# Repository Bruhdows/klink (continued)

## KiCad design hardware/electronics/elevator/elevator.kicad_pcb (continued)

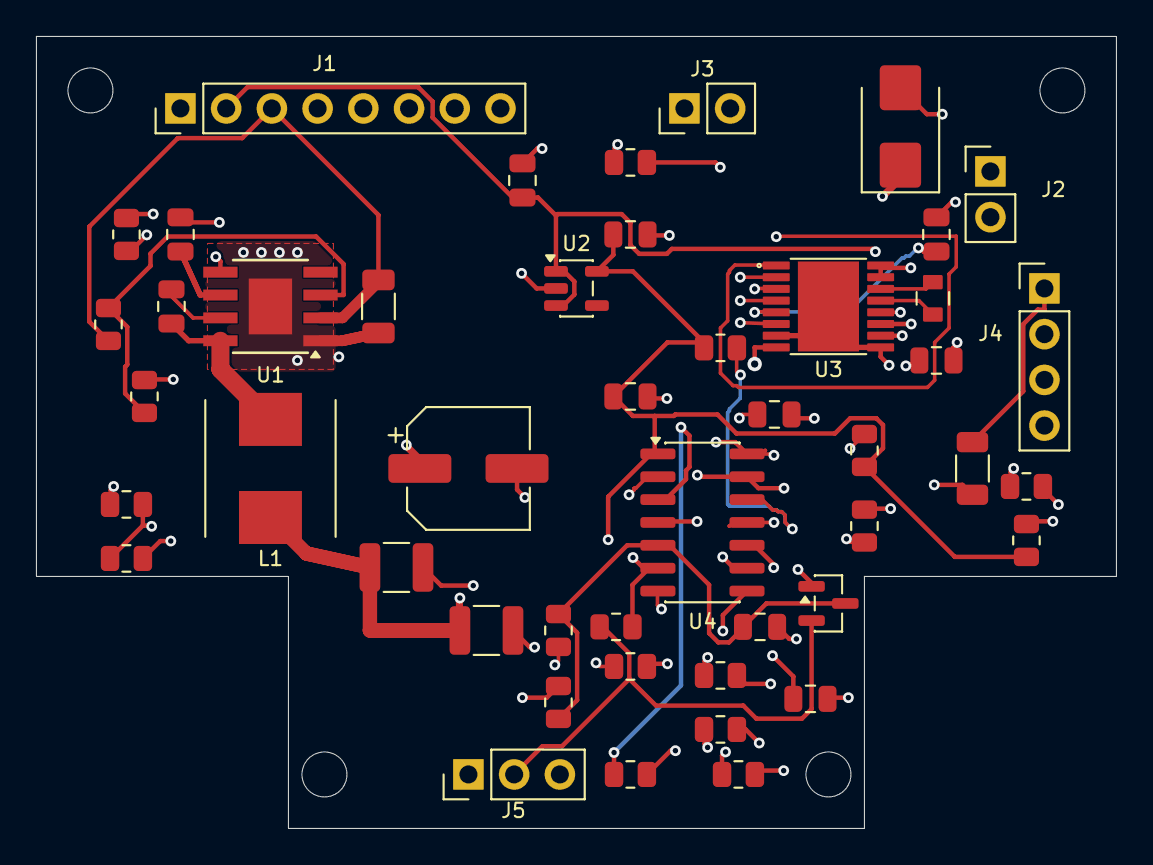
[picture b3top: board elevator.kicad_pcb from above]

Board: 4 copper layers, 60.0 x 44.0 mm, 51 parts (0 on the bottom side), 31 nets.

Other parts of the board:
H1, H2, H3, H4: MountingHole_2.5mm

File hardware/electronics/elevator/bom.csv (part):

Reference,Value,MPN,Alternate,TCR,Footprint,Quantity,purchase_url,unit_price,currency,price_status,checked_date,lcsc_reference
C1,10uF 50V X7R,C3216X7R1H106K160AC,,,Capacitor_SMD:C_1206_3216Metric,1,https://www.mouser.com/ProductDetail/TDK/C3216X7R1H106K160AC,0.35,USD,engineering allowance; NOT a verified supplier price,,
C2,100nF 50V X7R,C2012X7R1H104K125AE,,,Capacitor_SMD:C_0805_2012Metric,1,https://www.mouser.com/ProductDetail/TDK/C2012X7R1H104K125AE,0.1,USD,engineering allowance; NOT a verified supplier price,,
C3,1uF 16V,C2012X7R1H105K125AB,,,Capacitor_SMD:C_0805_2012Metric,1,https://www.mouser.com/ProductDetail/TDK/C2012X7R1H105K125AB,0.1,USD,engineering allowance; NOT a verified supplier price,,
C4,22uF 25V X7R,C1210C226K3RACTU,,,Capacitor_SMD:C_1210_3225Metric,1,https://www.mouser.com/ProductDetail/KEMET/C1210C226K3RACTU,0.35,USD,engineering allowance; NOT a verified supplier price,,
C5,22uF 25V X7R,C1210C226K3RACTU,,,Capacitor_SMD:C_1210_3225Metric,1,https://www.mouser.com/ProductDetail/KEMET/C1210C226K3RACTU,0.35,USD,engineering allowance; NOT a verified supplier price,,
C6,100uF 25V,EEH-ZC1E101XP,,,Capacitor_SMD:CP_Elec_6.3x7.7,1,https://www.mouser.com/ProductDetail/Panasonic/EEH-ZC1E101XP,1.5,USD,engineering allowance; NOT a verified supplier price,,
C7,1uF 16V,C2012X7R1H105K125AB,,,Capacitor_SMD:C_0805_2012Metric,1,https://www.mouser.com/ProductDetail/TDK/C2012X7R1H105K125AB,0.1,USD,engineering allowance; NOT a verified supplier price,,
C8,4.7uF 16V,C2012X7R1C475K125AB,,,Capacitor_SMD:C_0805_2012Metric,1,https://www.mouser.com/ProductDetail/TDK/C2012X7R1C475K125AB,0.1,USD,engineering allowance; NOT a verified supplier price,,
C9,100nF 50V X7R,C2012X7R1H104K125AE,,,Capacitor_SMD:C_0805_2012Metric,1,https://www.mouser.com/ProductDetail/TDK/C2012X7R1H104K125AE,0.1,USD,engineering allowance; NOT a verified supplier price,,
C10,100nF 50V X7R,C2012X7R1H104K125AE,,,Capacitor_SMD:C_0805_2012Metric,1,https://www.mouser.com/ProductDetail/TDK/C2012X7R1H104K125AE,0.1,USD,engineering allowance; NOT a verified supplier price,,
C11,22nF 50V,C2012C0G1H223J125AA,,,Klink:C_TDK_C2012_Reflow,1,https://www.mouser.com/ProductDetail/TDK/C2012C0G1H223J125AA,0.1,USD,engineering allowance; NOT a verified supplier price,,
C12,100nF 50V X7R,C2012X7R1H104K125AE,,,Capacitor_SMD:C_0805_2012Metric,1,https://www.mouser.com/ProductDetail/TDK/C2012X7R1H104K125AE,0.1,USD,engineering allowance; NOT a verified supplier price,,
C13,100nF 50V X7R,C2012X7R1H104K125AE,,,Capacitor_SMD:C_0805_2012Metric,1,https://www.mouser.com/ProductDetail/TDK/C2012X7R1H104K125AE,0.1,USD,engineering allowance; NOT a verified supplier price,,
C14,10nF 16V,CC0805KRX7R9BB103,,,Capacitor_SMD:C_0805_2012Metric,1,https://www.mouser.com/ProductDetail/Yageo/CC0805KRX7R9BB103,0.1,USD,engineering allowance; NOT a verified supplier price,,
C15,10nF 16V,CC0805KRX7R9BB103,,,Capacitor_SMD:C_0805_2012Metric,1,https://www.mouser.com/ProductDetail/Yageo/CC0805KRX7R9BB103,0.1,USD,engineering allowance; NOT a verified supplier price,,
D1,SMBJ13A-E3/52,SMBJ13A-E3/52,,,Diode_SMD:D_SMB,1,https://www.mouser.com/ProductDetail/Vishay/SMBJ13A-E3%2F52,0.35,USD,engineering allowance; NOT a verified supplier price,,
D2,"BAT54S,215","BAT54S,215",,,Package_TO_SOT_SMD:SOT-23,1,https://www.mouser.com/ProductDetail/Nexperia/BAT54S%2C215,0.15,USD,engineering allowance; NOT a verified supplier price,,
J1,MODULE_SERVICE,TSW-108-07-G-S,,,Connector_PinHeader_2.54mm:PinHeader_1x08_P2.54mm_Vertical,1,https://www.mouser.com/ProductDetail/Samtec/TSW-108-07-G-S,0.7,USD,engineering allowance; NOT a verified supplier price,,
J2,MOTOR,TSW-102-07-G-S,,,Connector_PinHeader_2.54mm:PinHeader_1x02_P2.54mm_Vertical,1,https://www.mouser.com/ProductDetail/Samtec/TSW-102-07-G-S,0.7,USD,engineering allowance; NOT a verified supplier price,,
J3,STOP_NC,TSW-102-07-G-S,,,Connector_PinHeader_2.54mm:PinHeader_1x02_P2.54mm_Vertical,1,https://www.mouser.com/ProductDetail/Samtec/TSW-102-07-G-S,0.7,USD,engineering allowance; NOT a verified supplier price,,
J4,INDEX_SENSOR,TSW-104-07-G-S,,,Connector_PinHeader_2.54mm:PinHeader_1x04_P2.54mm_Vertical,1,https://www.mouser.com/ProductDetail/Samtec/TSW-104-07-G-S,0.7,USD,engineering allowance; NOT a verified supplier price,,
J5,UPDI,TSW-103-07-G-S,,,Connector_PinHeader_2.54mm:PinHeader_1x03_P2.54mm_Vertical,1,https://www.mouser.com/ProductDetail/Samtec/TSW-103-07-G-S,0.7,USD,engineering allowance; NOT a verified supplier price,,
L1,33uH,SRP7050TA-330M,,,Klink:L_Bourns_SRP7050TA,1,https://www.mouser.com/ProductDetail/Bourns/SRP7050TA-330M,1.5,USD,engineering allowance; NOT a verified supplier price,,
R1,22k 1%,RC0805FR-0722KL,,,Resistor_SMD:R_0805_2012Metric,1,https://www.mouser.com/ProductDetail/Yageo/RC0805FR-0722KL,0.04,USD,engineering allowance; NOT a verified supplier price,,
R2,100k 1%,RC0805FR-07100KL,,,Resistor_SMD:R_0805_2012Metric,1,https://www.mouser.com/ProductDetail/Yageo/RC0805FR-07100KL,0.04,USD,engineering allowance; NOT a verified supplier price,,
R3,10k 1%,RC0805FR-0710KL,,,Resistor_SMD:R_0805_2012Metric,1,https://www.lcsc.com/product-detail/C84376.html,0.0049,USD,supplier reference listing; not a quote,2026-11-08,C84376
R4,110k 0.1%,RT0805BRD07110KL,,25ppm/K,Resistor_SMD:R_0805_2012Metric,1,https://www.mouser.com/ProductDetail/Yageo/RT0805BRD07110KL,0.3,USD,engineering allowance; NOT a verified supplier price,,
R5,10k 0.1%,RT0805BRD0710KL,,25ppm/K,Resistor_SMD:R_0805_2012Metric,1,https://www.lcsc.com/product-detail/C110775.html,0.0433,USD,supplier reference listing; not a quote,2026-11-08,C110775
R6,23.2k 0.1%,RT0805BRD0723K2L,,25ppm/K,Resistor_SMD:R_0805_2012Metric,1,https://www.mouser.com/ProductDetail/Yageo/RT0805BRD0723K2L,0.3,USD,engineering allowance; NOT a verified supplier price,,
R7,10k 0.1%,RT0805BRD0710KL,,25ppm/K,Resistor_SMD:R_0805_2012Metric,1,https://www.lcsc.com/product-detail/C110775.html,0.0433,USD,supplier reference listing; not a quote,2026-11-08,C110775
R8,2.87k 0.1%,RT0805BRD072K87L,,25ppm/K,Resistor_SMD:R_0805_2012Metric,1,https://www.mouser.com/ProductDetail/Yageo/RT0805BRD072K87L,0.3,USD,engineering allowance; NOT a verified supplier price,,
R9,10k 1%,RC0805FR-0710KL,,,Resistor_SMD:R_0805_2012Metric,1,https://www.lcsc.com/product-detail/C84376.html,0.0049,USD,supplier reference listing; not a quote,2026-11-08,C84376
R10,100k 1%,RC0805FR-07100KL,,,Resistor_SMD:R_0805_2012Metric,1,https://www.mouser.com/ProductDetail/Yageo/RC0805FR-07100KL,0.04,USD,engineering allowance; NOT a verified supplier price,,
R11,100k 1%,RC0805FR-07100KL,,,Resistor_SMD:R_0805_2012Metric,1,https://www.mouser.com/ProductDetail/Yageo/RC0805FR-07100KL,0.04,USD,engineering allowance; NOT a verified supplier price,,
R12,100k 1%,RC0805FR-07100KL,,,Resistor_SMD:R_0805_2012Metric,1,https://www.mouser.com/ProductDetail/Yageo/RC0805FR-07100KL,0.04,USD,engineering allowance; NOT a verified supplier price,,
R13,100k 1%,RC0805FR-07100KL,,,Resistor_SMD:R_0805_2012Metric,1,https://www.mouser.com/ProductDetail/Yageo/RC0805FR-07100KL,0.04,USD,engineering allowance; NOT a verified supplier price,,
R14,100k 1%,RC0805FR-07100KL,,,Resistor_SMD:R_0805_2012Metric,1,https://www.mouser.com/ProductDetail/Yageo/RC0805FR-07100KL,0.04,USD,engineering allowance; NOT a verified supplier price,,
R15,1k 1%,RC0805FR-071KL,,,Resistor_SMD:R_0805_2012Metric,1,https://www.mouser.com/ProductDetail/Yageo/RC0805FR-071KL,0.04,USD,engineering allowance; NOT a verified supplier price,,
R16,150k 1%,RC0805FR-07150KL,,,Resistor_SMD:R_0805_2012Metric,1,https://www.mouser.com/ProductDetail/Yageo/RC0805FR-07150KL,0.04,USD,engineering allowance; NOT a verified supplier price,,
R17,22k 1%,RC0805FR-0722KL,,,Resistor_SMD:R_0805_2012Metric,1,https://www.mouser.com/ProductDetail/Yageo/RC0805FR-0722KL,0.04,USD,engineering allowance; NOT a verified supplier price,,
R18,10k 1%,RC0805FR-0710KL,,,Resistor_SMD:R_0805_2012Metric,1,https://www.lcsc.com/product-detail/C84376.html,0.0049,USD,supplier reference listing; not a quote,2026-11-08,C84376
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
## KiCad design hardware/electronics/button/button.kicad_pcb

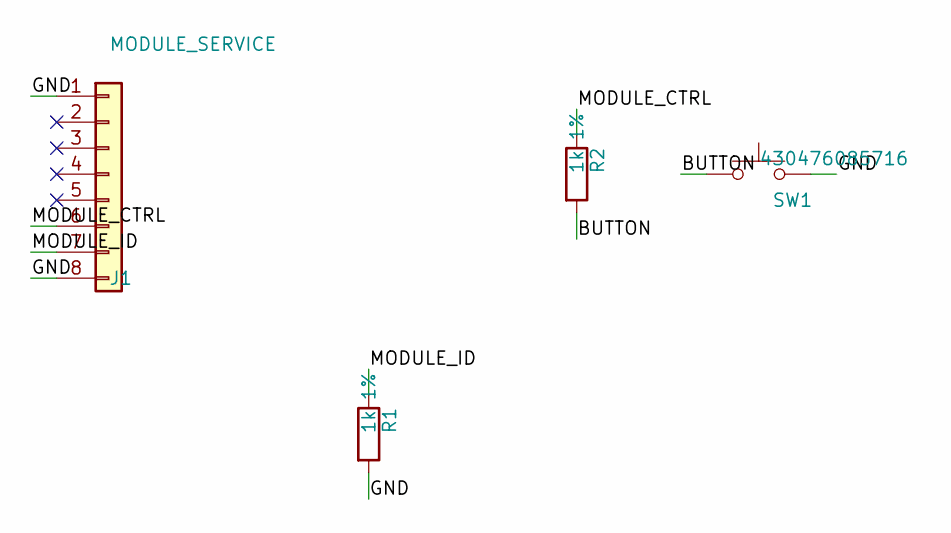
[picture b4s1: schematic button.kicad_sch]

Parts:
J1: MODULE_SERVICE; PinHeader_1x08_P2.54mm_Vertical; MPN M20-9990846
R1, R2: 1k 1%; R_0805_2012Metric; MPN RC0805FR-071KL
SW1: 430476085716; SW_PUSH-12mm_Wuerth-430476085716; MPN 430476085716

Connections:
/BUTTON: R2.2, SW1.1
/GND: J1.1, J1.8, R1.2, SW1.2
/MODULE_CTRL: J1.6, R2.1
/MODULE_ID: J1.7, R1.1

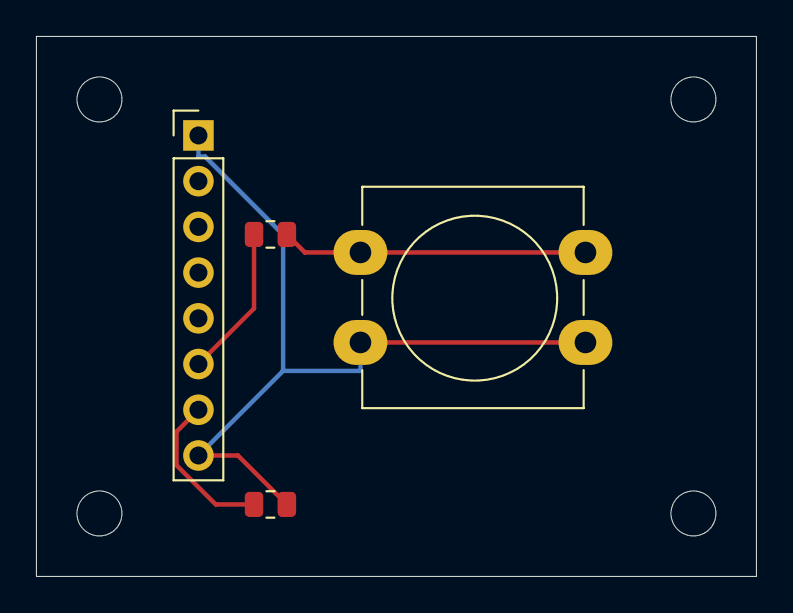
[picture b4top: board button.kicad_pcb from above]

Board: 2 copper layers, 40.0 x 30.0 mm, 8 parts (0 on the bottom side), 4 nets.

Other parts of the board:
H1, H2, H3, H4: MountingHole_2.5mm

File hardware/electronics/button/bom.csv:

Reference,Value,MPN,Footprint,Assembly,Quantity,Qty_for_two_prototypes,Datasheet,purchase_url,unit_price,currency,price_status,checked_date
J1,MODULE_SERVICE,M20-9990846,Connector_PinHeader_2.54mm:PinHeader_1x08_P2.54mm_Vertical,PCB,1,2,,https://www.mouser.com/ProductDetail/Harwin/M20-9990846,0.7,USD,engineering allowance; NOT a verified supplier price,
R1,1k 1%,RC0805FR-071KL,Resistor_SMD:R_0805_2012Metric,PCB,1,2,,https://www.mouser.com/ProductDetail/Yageo/RC0805FR-071KL,0.04,USD,engineering allowance; NOT a verified supplier price,
R2,1k 1%,RC0805FR-071KL,Resistor_SMD:R_0805_2012Metric,PCB,1,2,,https://www.mouser.com/ProductDetail/Yageo/RC0805FR-071KL,0.04,USD,engineering allowance; NOT a verified supplier price,
SW1,430476085716,430476085716,Button_Switch_THT:SW_PUSH-12mm_Wuerth-430476085716,PCB,1,2,https://www.we-online.com/components/products/datasheet/4304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,https://www.mouser.com/ProductDetail/Wurth-Elektronik/430476085716,1.2,USD,engineering allowance; NOT a verified supplier price,

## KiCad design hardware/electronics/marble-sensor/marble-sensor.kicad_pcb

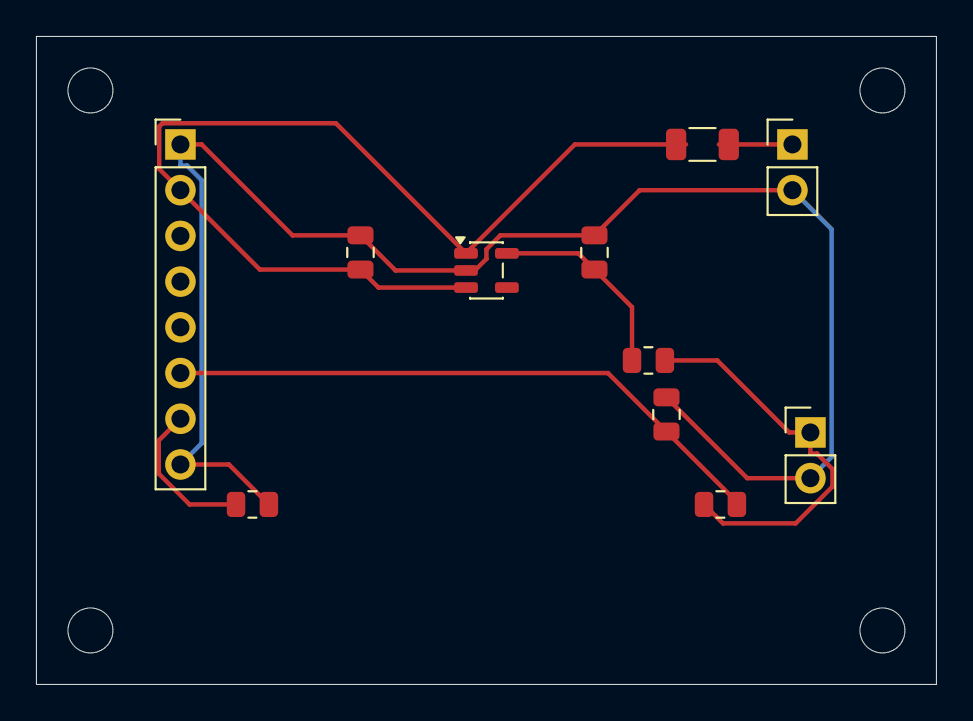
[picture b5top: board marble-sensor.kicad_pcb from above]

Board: 2 copper layers, 50.0 x 36.0 mm, 15 parts (0 on the bottom side), 7 nets.

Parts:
C1, C2: 1uF 16V; C_0805_2012Metric
C3: 1nF 50V; C_0805_2012Metric
H1, H2, H3, H4: MountingHole_2.5mm
J1: MODULE_SERVICE; PinHeader_1x08_P2.54mm_Vertical
J2: IR_EMITTER; PinHeader_1x02_P2.54mm_Vertical
J3: PHOTOTRANSISTOR_C_E; PinHeader_1x02_P2.54mm_Vertical
R1: 2.2k 1%; R_0805_2012Metric
R2: 220 1% 0.25W; R_1206_3216Metric
R3: 10k 1%; R_0805_2012Metric
R4: 1k 1%; R_0805_2012Metric
U1: AP2112K-3.3TRG1; SOT-23-5

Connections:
/GND: C1.2, C2.2, C3.2, J1.1, J1.8, J2.2, J3.2, R1.2, U1.2
/IR_ANODE: J2.1, R2.2
/MODULE_5V: C1.1, J1.2, R2.1, U1.1, U1.3
/MODULE_CTRL: C3.1, J1.6, R4.2
/MODULE_ID: J1.7, R1.1
/SENSE: J3.1, R3.2, R4.1
/SENSOR_3V3: C2.1, R3.1, U1.5

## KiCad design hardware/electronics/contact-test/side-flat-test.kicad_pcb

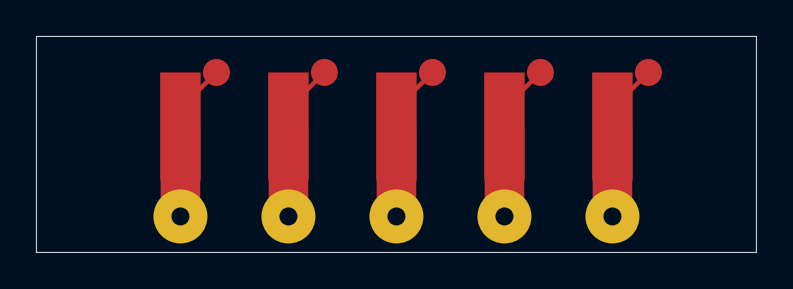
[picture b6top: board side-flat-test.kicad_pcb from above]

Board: 2 copper layers, 40.0 x 12.0 mm, 15 parts (0 on the bottom side), 5 nets.

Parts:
J1, J2, J3, J4, J5: TIN MATE TEST
TP1, TP2, TP3, TP4, TP5: FORCE
TP6, TP7, TP8, TP9, TP10: SENSE

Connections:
CHANNEL_1: J1.1, TP1.1, TP6.1
CHANNEL_2: J2.1, TP2.1, TP7.1
CHANNEL_3: J3.1, TP3.1, TP8.1
CHANNEL_4: J4.1, TP4.1, TP9.1
CHANNEL_5: J5.1, TP5.1, TP10.1

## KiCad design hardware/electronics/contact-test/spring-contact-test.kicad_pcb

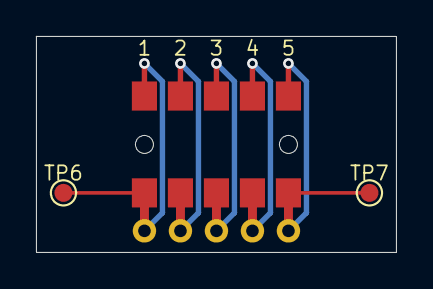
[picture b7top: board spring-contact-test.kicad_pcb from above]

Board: 2 copper layers, 20.0 x 12.0 mm, 8 parts (0 on the bottom side), 5 nets.

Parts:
J1: UNQUALIFIED CONTACT TEST; SAMZO_03E315320_TestOnly
TP1: CH1
TP2: CH2
TP3: CH3
TP4: CH4
TP5: CH5
TP6: CH1_SENSE; TestPoint_Pad_D1.0mm
TP7: CH5_SENSE; TestPoint_Pad_D1.0mm

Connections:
CH1: J1.1, TP1.1, TP6.1
CH2: J1.2, TP2.1
CH3: J1.3, TP3.1
CH4: J1.4, TP4.1
CH5: J1.5, TP5.1, TP7.1

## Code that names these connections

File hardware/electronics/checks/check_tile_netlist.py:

#!/usr/bin/env python3
"""Check Rev A connectivity in native KiCad XML. Does not verify component behavior or qualification."""
import argparse
import xml.etree.ElementTree as ET


def inspect(path):
    root = ET.parse(path).getroot()
    nets, members = {}, {}
    for net in root.findall('./nets/net'):
        name = net.attrib['name'].removeprefix('/')
        members[name] = set()
        for node in net.findall('node'):
            key = (node.attrib['ref'],node.attrib['pin'])
            if key in nets:
                raise ValueError(f'Duplicate pin in netlist: {key}')
            nets[key] = name
            members[name].add(key)
    checks = 0

    def expect(ref,pin,name):
        nonlocal checks
        actual = nets.get((ref,str(pin)))
        if actual != name:
            raise ValueError(f'{ref}.{pin}: expected {name}, got {actual}')
        checks += 1

    def disconnected(ref,pin):
        nonlocal checks
        if 'unconnected-' not in nets.get((ref,str(pin)),''):
            raise ValueError(f'{ref}.{pin}: expected a deliberate no-connect')
        checks += 1

    mcu={2:'+3V3',3:'MODULE_20V_EN',4:'MODULE_20V_FAULT',5:'BUS_SENSE',6:'N_DETECT',
         7:'E_TX',8:'E_RX',9:'E_DETECT',10:'MODULE_5V_FAULT',11:'MODULE_ID',12:'RGB_DATA',
         13:'W_TX',14:'S_TX',15:'S_RX',16:'W_RX',17:'MODULE_IO_REQUEST',18:'MODULE_5V_EN',
         19:'EDGE_IO_DISABLE',20:'LOCAL_POWER_FAULT',21:'N_TX',22:'N_RX',23:'MODULE_CTRL',
         24:'DEBUG_DCK',25:'DEBUG_DIO',26:'MODULE_SCL',27:'MODULE_SDA',29:'GND'}
    for pin,name in mcu.items():expect('U1',pin,name)
    for ref,d,reverse in [('J3','N',False),('J6','E',False),('J4','S',True),('J5','W',True)]:
        detect=d+'_DETECT'+('_EDGE' if d in 'NE' else '')
        order=[d+'_20V','GND',d+'_TX_EDGE',d+'_RX_EDGE',detect]
        if reverse:order=[detect,d+'_TX_EDGE',d+'_RX_EDGE','GND',d+'_20V']
        for pin,name in enumerate(order,1):expect(ref,pin,name)
    for pin,name in enumerate(['GND','MODULE_5V','MODULE_20V','MODULE_SDA_PAD','MODULE_SCL_PAD',
                                'MODULE_CTRL_PAD','MODULE_ID_PAD','GND'],1):expect('J7',pin,name)
    groups={
        'U4':{1:'GND',2:'TILE_20V',3:'BUCK_EN',5:'BUCK_FB',6:'BUCK_VCC',7:'BUCK_BST',8:'BUCK_SW',9:'GND'},
        'U5':{1:'TILE_20V',2:'TILE_20V',3:'MODULE_RTN',5:'EFUSE_OVLO',6:'MODULE_MODE',7:'MODULE_20V_SHDN',8:'MODULE_RTN',9:'GND',11:'EFUSE_ILM',12:'EFUSE_DVDT',14:'MODULE_20V_FAULT',15:'MODULE_20V',16:'MODULE_20V',17:'MODULE_RTN'},
        'U7':{1:'LOCAL_20V_RAW',2:'LOCAL_20V_RAW',3:'LOCAL_RTN',5:'LOCAL_OVP',6:'LOCAL_MODE',8:'LOCAL_RTN',9:'GND',11:'LOCAL_ILIM',12:'LOCAL_DVDT',14:'LOCAL_POWER_FAULT',15:'TILE_20V',16:'TILE_20V',17:'LOCAL_RTN'},
        'U3':{1:'MODULE_5V_EN',2:'MODULE_5V_OVLO',4:'MODULE_5V_FAULT',5:'+5V',6:'MODULE_5V',7:'MODULE_5V_DVDT',8:'GND',9:'MODULE_5V_ILIM'},
        'U6':{1:'GND',2:'RGB_DATA',3:'GND',4:'RGB_BUFFER_OUT',5:'+5V'},
        'U12':{1:'MODULE_IO_ENABLE',2:'MODULE_SCL',3:'MODULE_SCL_PAD',4:'MODULE_IO_ENABLE',5:'MODULE_SDA',6:'MODULE_SDA_PAD',7:'GND',8:'MODULE_CTRL_PAD',9:'MODULE_CTRL',10:'MODULE_IO_ENABLE',11:'MODULE_ID_PAD',12:'MODULE_ID',13:'+3V3',14:'+3V3'},
        'U13':{1:'+3V3',2:'BUS_SENSE_RAW',3:'BUS_SENSE',4:'+3V3',5:'N_DETECT_EDGE',6:'N_DETECT',7:'GND',8:'E_DETECT',9:'E_DETECT_EDGE',10:'+3V3',13:'GND',14:'+3V3'},
        'U14':{1:'MODULE_5V_GOOD',2:'GND',3:'+3V3',5:'MODULE_5V_SENSE',6:'+3V3'},
        'U15':{1:'MODULE_5V_GOOD',2:'MODULE_IO_REQUEST',3:'GND',4:'MODULE_IO_ENABLE',5:'+3V3'},
        'F1':{1:'BUS_20V',2:'LOCAL_20V_RAW'}, 'L1':{1:'BUCK_SW',2:'+5V'},
        'C10':{1:'BUCK_BST',2:'BUCK_SW'},'C24':{1:'BUCK_VCC',2:'GND'},
        'D1':{1:'+5V',2:'RGB_CHAIN',3:'GND',4:'RGB_DIN'},
        'D3':{1:'+5V',2:'RGB_DOUT_TEST',3:'GND',4:'RGB_CHAIN'},
        'R3':{1:'RGB_BUFFER_OUT',2:'RGB_DIN'},
        'R11':{1:'TILE_20V',2:'BUS_SENSE_RAW'},'R12':{1:'BUS_SENSE_RAW',2:'GND'},
        'R15':{1:'MODULE_20V_SHDN',2:'MODULE_RTN'}, 'R16':{1:'EFUSE_ILM',2:'MODULE_RTN'},
        'R18':{1:'EFUSE_OVLO',2:'MODULE_RTN'},'C17':{1:'EFUSE_DVDT',2:'MODULE_RTN'},
        'R21':{1:'LOCAL_ILIM',2:'LOCAL_RTN'},'R22':{1:'LOCAL_MODE',2:'LOCAL_RTN'},
        'R23':{1:'MODULE_MODE',2:'MODULE_RTN'},'R24':{1:'MODULE_20V_EN',2:'MODULE_20V_SHDN'},
        'R25':{1:'LOCAL_20V_RAW',2:'LOCAL_OVP'},'R26':{1:'LOCAL_OVP',2:'LOCAL_RTN'},
        'R28':{1:'+5V',2:'BUCK_FB'},'R29':{1:'BUCK_FB',2:'GND'},
        'R46':{1:'+3V3',2:'EDGE_IO_DISABLE'},'R47':{1:'MODULE_IO_REQUEST',2:'GND'},
        'R48':{1:'+3V3',2:'MODULE_5V_GOOD'},'R49':{1:'MODULE_5V',2:'GND'},
        'R50':{1:'+3V3',2:'GND'},'R51':{1:'MODULE_5V',2:'MODULE_5V_SENSE'},
        'R52':{1:'MODULE_5V_SENSE',2:'GND'},'R53':{1:'MODULE_5V_ILIM',2:'GND'},'R54':{1:'+5V',2:'MODULE_5V_OVLO'},'R55':{1:'MODULE_5V_OVLO',2:'GND'},'C33':{1:'MODULE_5V_DVDT',2:'GND'},
    }
    for i,d in enumerate('NESW'):
        groups['U'+str(i+8)]={1:'EDGE_IO_DISABLE',2:d+'_TX',3:d+'_RX',4:'GND',5:d+'_RX_IN',6:d+'_TX_DRV',7:'EDGE_IO_DISABLE',8:'+3V3'}
        for j,(a,b) in enumerate([(d+'_TX_DRV',d+'_TX_EDGE'),(d+'_RX_EDGE',d+'_RX_IN'),('+3V3',d+'_TX'),('+3V3',d+'_RX_IN')]):
            groups['R'+str(30+i*4+j)]={1:a,2:b}
    for ref,pins in groups.items():
        for pin,name in pins.items():expect(ref,pin,name)
    for ref,d in [('F2','N'),('F3','E'),('F4','S'),('F5','W')]:
        expect(ref,1,d+'_20V');expect(ref,2,'BUS_20V')
    for i,net in enumerate(['BUS_20V','LOCAL_20V_RAW','TILE_20V','MODULE_20V'],4):
        expect('D'+str(i),1,net);expect('D'+str(i),2,'GND')
    for pin,net in enumerate(['BUS_20V','TILE_20V','+5V','+3V3','MODULE_5V','MODULE_20V','GND','RGB_DOUT_TEST'],1):expect('TP'+str(pin),1,net)
    for pin in [1,28]:disconnected('U1',pin)
    for ref,pins in [('U3',[3,10]),('U4',[4]),('U5',[10]),('U7',[7,10]),('U13',[11,12]),('U14',[4])]:
        for pin in pins:disconnected(ref,pin)
    # These boundaries must remain separate even if an ERC-clean accidental wire is introduced.
    for names in [('GND','LOCAL_RTN','MODULE_RTN'),('BUS_20V','LOCAL_20V_RAW','TILE_20V'),
                  ('BUS_SENSE','BUS_SENSE_RAW'),*(('MODULE_'+s,'MODULE_'+s+'_PAD') for s in ['SDA','SCL','CTRL','ID'])]:
        if len({frozenset(members[n]) for n in names}) != len(names):raise ValueError(f'Isolation boundary shorted: {names}')
        checks += 1
    components=root.findall('./components/comp')
    missing=[c.attrib['ref'] for c in components if not c.findtext('footprint') and not any(
        p.attrib['name']=='exclude_from_board' for p in c.findall('property'))]
    return checks,len(components),len(members),missing


def main():
    parser=argparse.ArgumentParser(description=__doc__);parser.add_argument('netlist');args=parser.parse_args()
    try:checks,components,nets,missing=inspect(args.netlist)
    except (ValueError,KeyError) as e:raise SystemExit(str(e))
    print(f'PASS: {checks} connectivity checks; {components} components; {nets} nets.')
    print('Missing onboard footprints: '+', '.join(missing))
    print('Connectivity checks do not establish transient survival, Ioff performance, fuse coordination or mechanical qualification.')


if __name__=='__main__':main()
